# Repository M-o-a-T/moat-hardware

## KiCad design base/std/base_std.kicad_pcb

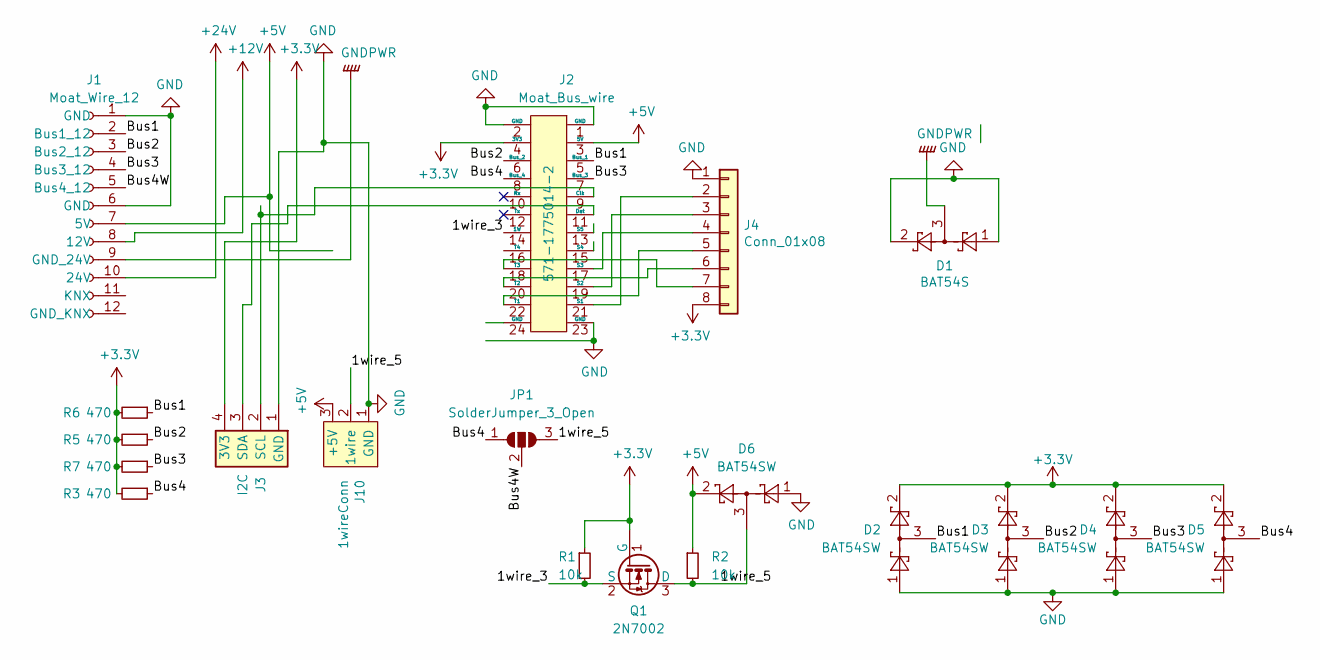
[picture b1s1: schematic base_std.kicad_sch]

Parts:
D1: BAT54S; SOT-23
D2, D3, D4, D5, D6: BAT54SW; SOT-23
J1: Moat_Wire_12; MoaT_12_Pin_V
J2: Moat_Bus_wire; TE_1775014_socket; Digikey A118067CT-ND
J3: I2C; AVX_9276_4Pin_HS
J4: Conn_01x08; PinHeader_1x08_P2.54mm_Vertical
J10: 1wireConn; AVX_9276_3Pin
JP1: SolderJumper_3_Open; SolderJumper-3_P2.0mm_Open_TrianglePad1.0x1.5mm_NumberLabels
Q1: 2N7002; SOT-23
R1, R2: 10k; R_0603_1608Metric
R3, R5, R6, R7: 470; R_0603_1608Metric

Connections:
+3V3: D2.2, D3.2, D4.2, D5.2, J2.4 (3V3), J3.4 (3V3), J4.8, Q1.1 (G), R1.1, R3.2, R5.2, R6.2, R7.2
+5V: D6.2, J1.7 (5V), J2.3 (5V), J10.3 (+5V), R2.1
+12V: J1.8 (12V)
+24V: J1.10 (24V)
/1wire_3: J2.14 (1W), Q1.2 (S), R1.2
/1wire_5: D6.3, J10.2 (1wire), JP1.3 (B), Q1.3 (D), R2.2
/Bus1: D2.3, J1.2 (Bus1_12), J2.5 (Bus_1), R6.1
/Bus2: D3.3, J1.3 (Bus2_12), J2.6 (Bus_2), R5.1
/Bus3: D4.3, J1.4 (Bus3_12), J2.7 (Bus_3), R7.1
/Bus4: D5.3, J2.8 (Bus_4), JP1.1 (A), R3.1
/Bus4W: J1.5 (Bus4_12), JP1.2 (C)
GND: D1.1, D1.2, D2.1, D3.1, D4.1, D5.1, D6.1, J1.1 (GND), J1.6 (GND), J2.1 (GND), J2.2 (GND), J2.23 (GND), J3.1 (GND), J4.1, J10.1 (GND)
GNDPWR: D1.3, J1.9 (GND_24V)
unnamed: J2.9 (Clk), J3.2 (SCL)
unnamed: J2.11 (Dat), J3.3 (SDA)
unnamed: J2.21 (S1), J4.2
unnamed: J2.19 (S2), J4.3
unnamed: J2.17 (S3), J4.4
unnamed: J2.22 (T1), J4.5
unnamed: J2.20 (T2), J4.6
unnamed: J2.18 (T3), J4.7

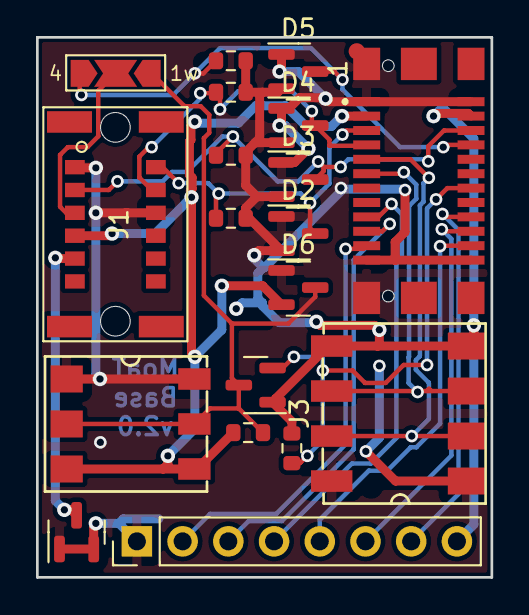
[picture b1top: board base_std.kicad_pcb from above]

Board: 2 copper layers, 25.2 x 30.0 mm, 19 parts (0 on the bottom side), 19 nets.

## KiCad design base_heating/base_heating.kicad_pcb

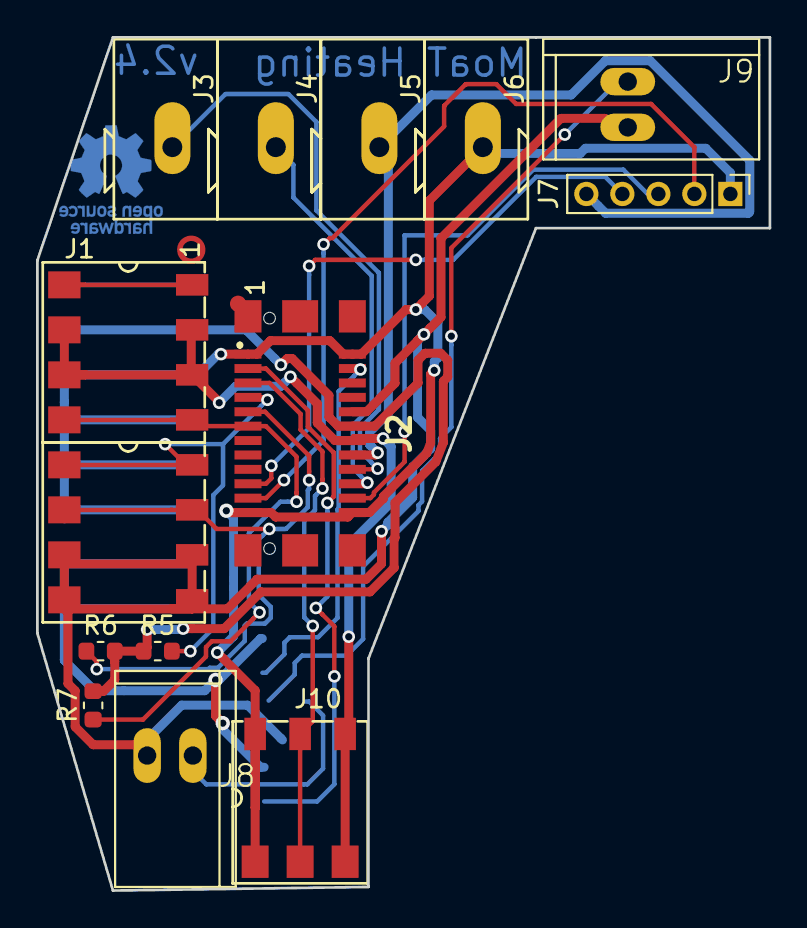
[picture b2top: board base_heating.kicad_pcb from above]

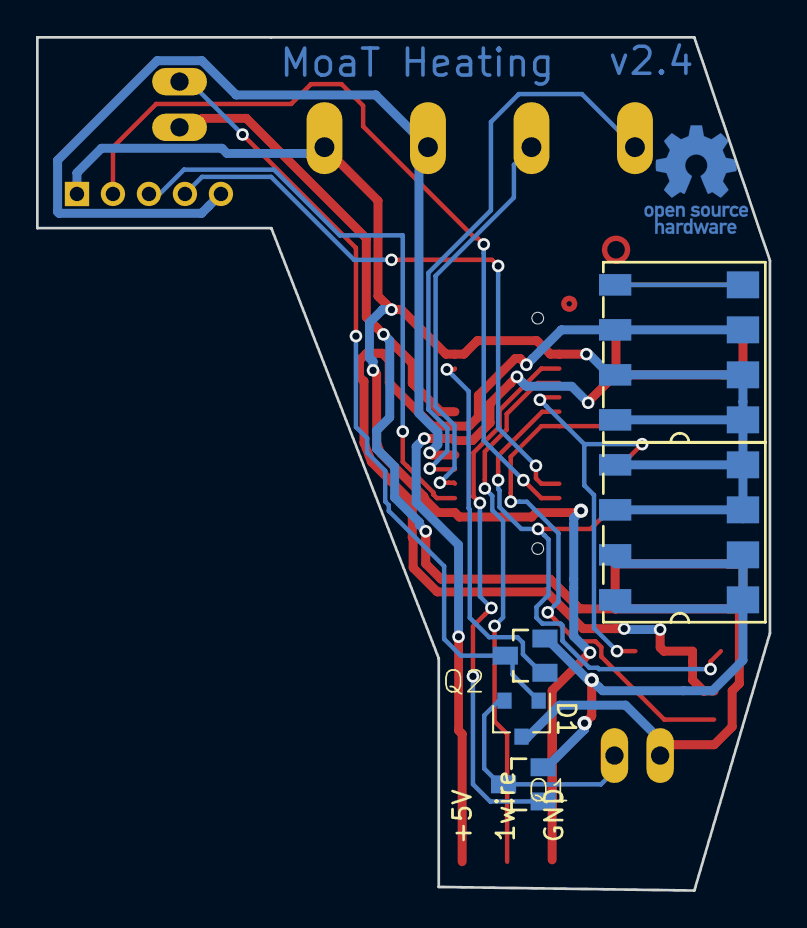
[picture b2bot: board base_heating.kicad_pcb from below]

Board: 2 copper layers, 40.7 x 47.4 mm, 16 parts (3 on the bottom side), 19 nets.

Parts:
D1: BAT54C; SOT-23
J1: Moat_Bus_16; Moat_16_2side
J2: Moat_Bus_wire; TE_1775014_socket
J3: SCLK; Wago_Terminal_243
J4: SDA; Wago_Terminal_243
J5: 3V3; Wago_Terminal_243
J6: GND; Wago_Terminal_243
J7: Conn_01x05; PinHeader_1x05_P2.00mm_Vertical
J8: S1; 1X02_GN
J9: S2; 1X02_GN
J10: 1wireConn; AVX_9276_3Pin
Q1, Q2: 2N7002; SOT23
R5, R6, R7: 470; R_0603_1608Metric

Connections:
+5V: J1.3 (5V), J1.5 (5V), J2.14 (5V), J10.3 (+5V)
+12V: J1.4 (12V), J2.12 (12V), R5.1, R6.2, R7.2
+24V: D1.3, J1.13 (24V), J1.15 (24V), J2.10 (Vcc), J8.2, J9.2
/S1: J2.3 (S1), Q1.1 (G)
/S2: J2.4 (S2), Q2.1 (G)
GNDPWR: J1.14 (GND_24), J1.16 (GND_24), Q1.2 (S), Q2.2 (S)
unnamed: J1.11 (Bus1_12), J2.9 (Bus2_12), R6.1
unnamed: J1.9 (Bus2_12), J2.7 (Bus1_12), R5.2
unnamed: J1.7 (Bus3_12), J2.11 (Bus3_12), R7.1
unnamed: J1.6 (GND), J1.8 (GND), J1.10 (GND), J1.12 (GND), J2.1 (GND), J2.2 (GND), J2.23 (GND), J2.24 (GND), J6.1, J7.1, J10.1 (GND)
unnamed: J2.16 (3V3), J5.1, J7.5
unnamed: J2.18 (CLK), J3.1
unnamed: J2.20 (DAT), J4.1
unnamed: J2.21 (T1), J7.2
unnamed: J2.22 (T2), J7.3
unnamed: J2.19 (T3), J7.4
unnamed: J2.5 (1wire_5), J10.2 (1wire)
unnamed: D1.2, J8.1, Q1.3 (D)
unnamed: D1.1, J9.1, Q2.3 (D)

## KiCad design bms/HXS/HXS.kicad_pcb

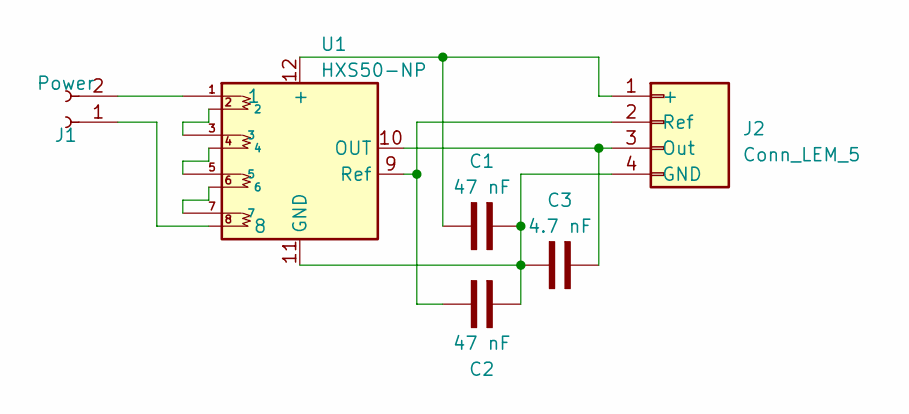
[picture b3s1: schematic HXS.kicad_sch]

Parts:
C1, C2: C_47n_0603; C_0603_1608Metric; Farnell 3013432
C3: C_4n7_0603; C_0603_1608Metric; Farnell 2812325
J1: Power; Conn_P5.0mm_2_Lumberg
J2: Conn_LEM_5; JST_PH_B4B-PH-K_1x04_P2.00mm_Vertical
U1: HXS50-NP; LEM_HXS_50-NP

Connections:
unnamed: J1.2, U1.1
unnamed: C1.1, J2.1 (+), U1.12 (+)
unnamed: C1.2, C2.2, C3.1, J2.4 (GND), U1.11 (GND)
unnamed: C3.2, J2.3 (Out), U1.10 (OUT)
unnamed: C2.1, J2.2 (Ref), U1.9 (Ref)
unnamed: U1.2, U1.3
unnamed: U1.4, U1.5
unnamed: U1.6, U1.7
unnamed: J1.1, U1.8

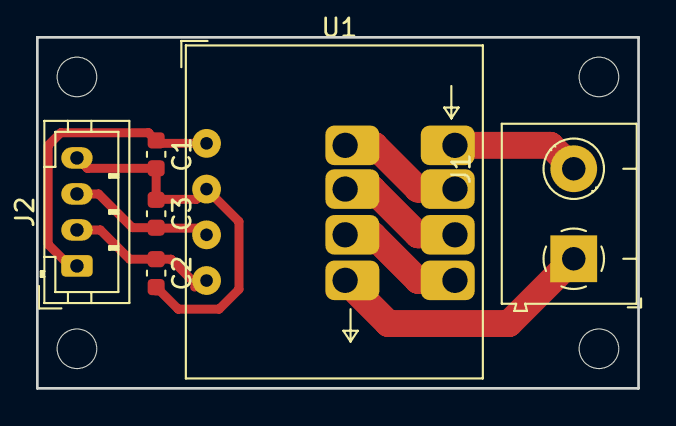
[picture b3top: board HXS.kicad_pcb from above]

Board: 2 copper layers, 33.4 x 19.5 mm, 6 parts (0 on the bottom side), 9 nets.

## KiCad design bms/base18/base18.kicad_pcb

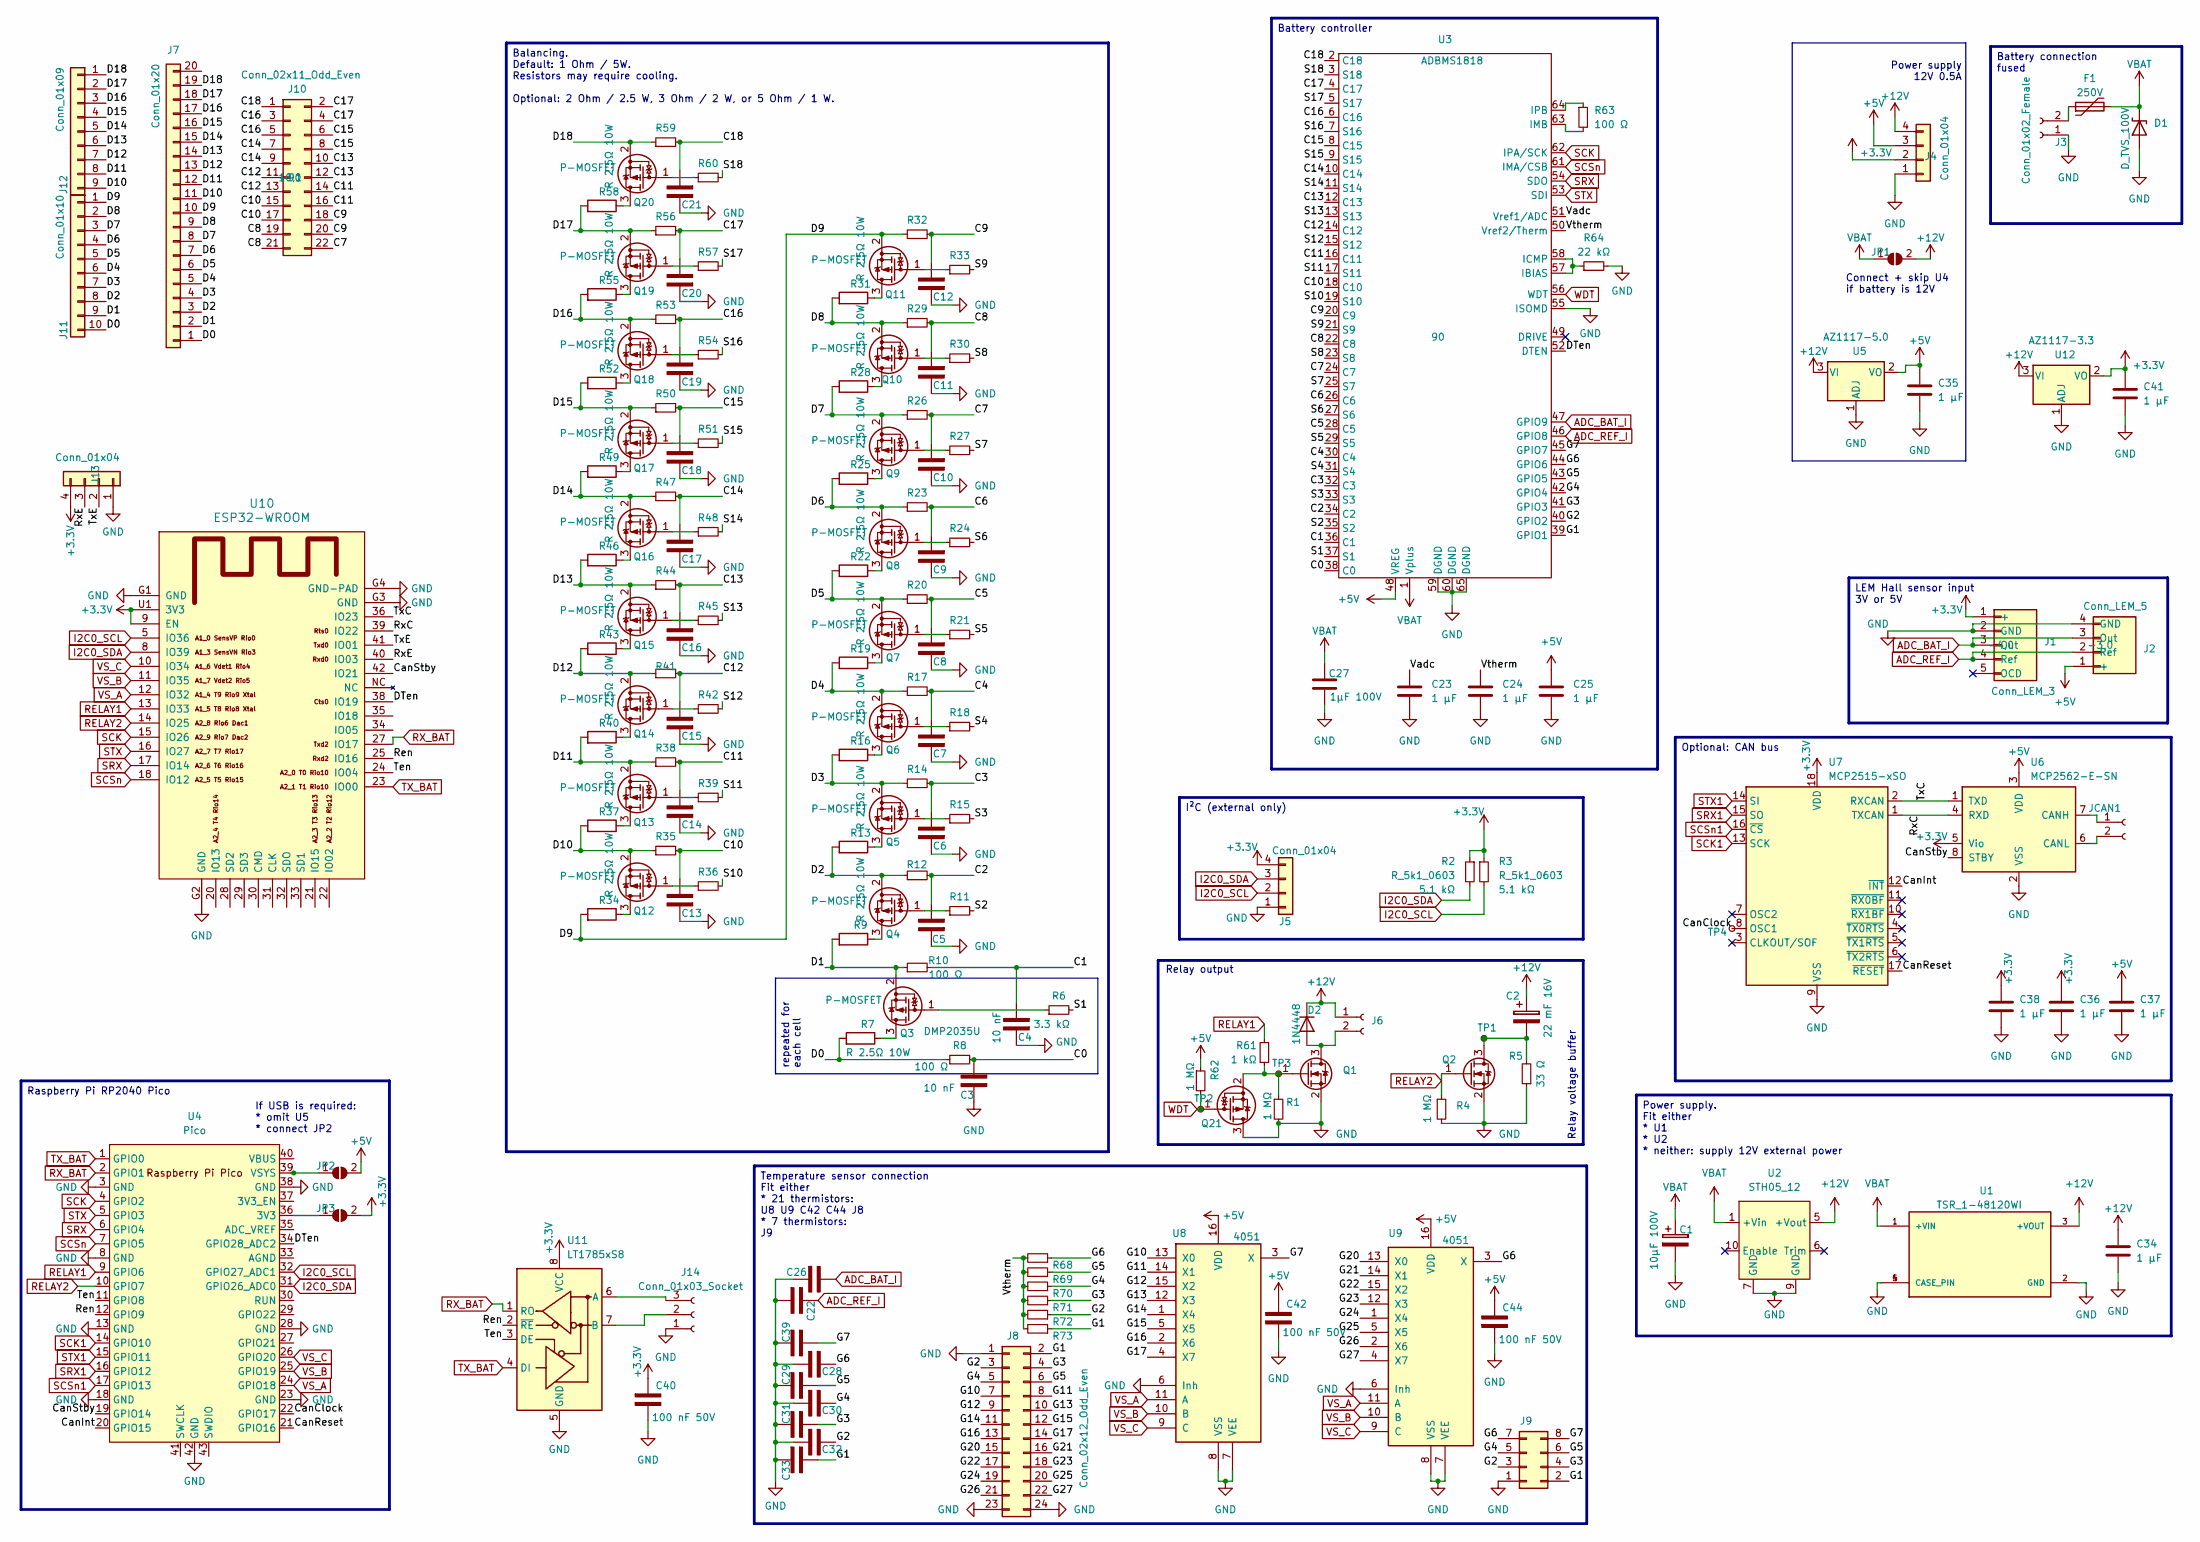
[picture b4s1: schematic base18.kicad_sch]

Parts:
C1: CP_10µ_100V_6m3; CP_Elec_6.3x7.7; Farnell 2068705
C2: CP_22m_16V; CP_Radial_D22.0mm_P10.00mm_SnapIn; LCSC C315548
C3, C4, C5, C6, C7, C8, C9, C10, C11, C12, C13, C14, C15, C16, C17, C18, C19, C20, C21, C22, C26, C28, C29, C30, C31, C32, C33, C39, C40, C42, C44: CP_100n_50V_0603; C_0603_1608Metric; LCSC C14663
C23, C24, C25: CP_1µ_10V_0603; C_0603_1608Metric; Farnell 3013419
C27: CP_1µ_100V_0805; R_0805_2012Metric; Farnell 3243166
C34, C35, C36, C37, C38, C41: C_1µ_25V_0603; C_0603_1608Metric; Farnell 3581460
D1: D_TVS_100V; D_SMB; Farnell 3996927
D2: 1N4448; D_SOD-123; LCSC C124191
F1: FuseHolder; Fuseholder_Cylinder-5x20mm_Stelvio-Kontek_PTF78_Horizontal_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; Farnell 2461158
J1: Conn_LEM_3; JST_PH_B5B-PH-K_1x05_P2.00mm_Vertical; LCSC C157993
J2: Conn_LEM_5; JST_PH_B4B-PH-K_1x04_P2.00mm_Vertical; LCSC C131334
J3: Conn_01x02_Female; Esto02
J4, J5, J13: Conn_01x04; PinHeader_1x04_P2.54mm_Vertical
J6: Conn_01x02_Female; Conn_P5.0mm_2_Lumberg
J7: Conn_01x20; PinHeader_1x20_P2.54mm_Horizontal
J8: Conn_02x12_Odd_Even; PinHeader_2x12_P2.54mm_Vertical
J9: Conn_02x04_Odd_Even; PinHeader_2x04_P2.54mm_Vertical
J10: Conn_02x11_Odd_Even; PinHeader_2x11_P2.00mm_Vertical; LCSC C2905997
J11: Conn_01x10; PinSocket_1x10_P2.00mm_Horizontal; LCSC C158038
J12: Conn_01x09; PinSocket_1x09_P2.00mm_Horizontal; LCSC C157968
J14: Conn_01x03_Socket; PinHeader_1x03_P2.54mm_Vertical
JCAN1: Conn_01x02_Female; Esto02
JP1, JP2, JP3: Bat12V; SolderJumper-2_P1.3mm_Open_RoundedPad1.0x1.5mm
Q1, Q2: DMN2058U; SOT-23; Farnell 2709530
Q3, Q4, Q5, Q6, Q7, Q8, Q9, Q10, Q11, Q12, Q13, Q14, Q15, Q16, Q17, Q18, Q19, Q20, Q21: DMP2035U; SOT-23; Farnell 2061419
R1, R4, R62: R_1M_0603; R_0603_1608Metric; LCSC C22935
R2, R3: R_5k1_0603; R_0603_1608Metric; LCSC C23186
R5: R_33_0603; R_0603_1608Metric; LCSC C25232
R6, R11, R15, R18, R21, R24, R27, R30, R33, R36, R39, R42, R45, R48, R51, R54, R57, R60: R_3k3_0603; R_0603_1608Metric; LCSC C22978
R7, R9, R13, R16, R19, R22, R25, R28, R31, R34, R37, R40, R43, R46, R49, R52, R55, R58: R_2.5_10W; R_Radial_Power_L12.5mm_W9.0mm_P5.00mm; LCSC C216394
R8, R10, R12, R14, R17, R20, R23, R26, R29, R32, R35, R38, R41, R44, R47, R50, R53, R56, R59, R63: R_100_0603; R_0603_1608Metric; LCSC C22775
R61: R_1k_0603; R_0603_1608Metric; LCSC C21190
R64: R_22k_0603; R_0603_1608Metric; LCSC C31850
R68, R69, R70, R71, R72, R73: R_10k_0603; R_0603_1608Metric; LCSC C25804
TP1, TP2, TP3, TP4: TestPoint_Small; TestPoint_Pad_D1.0mm
U1: TSR_1-48120WI; TSR_1-48xxWI; PARTREV April 7, 2021; Farnell 3255316
U2: STH05_12; STH05; Farnell 3212472
U3: ADBMS1818; LQFP-64-1EP_10x10mm_P0.5mm_EP5x5mm_ThermalVias; Farnell 4027982
U4: Pico; RPi_Pico_SMD
U5: AZ1117-5.0; SOT-223; LCSC C526405
U6: MCP2562-E-SN; SOIC-8_3.9x4.9mm_P1.27mm; JLCRotOffset -90
U7: MCP2515-xSO; SOIC-18W_7.5x11.6mm_P1.27mm; Farnell 1605565
U8, U9: 4051; SOIC-16_3.9x9.9mm_P1.27mm; Farnell 1201327
U10: ESP32-WROOM; Digikey 1904-1024-1-ND
U11: LT1785xS8; SOIC-8_3.9x4.9mm_P1.27mm; LCSC C468242
U12: AZ1117-3.3; SOT-223; LCSC C108492

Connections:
+3V3: C36.1, C38.1, C40.1, C41.1, J1.1 (+), J4.2, J5.4, J13.4, JP3.2 (B), R2.1, R3.1, U6.5 (Vio), U7.18 (VDD), U10.9 (EN), U10.U1 (3V3), U11.8 (VCC), U12.2 (VO)
+5V: C25.1, C35.1, C37.1, C42.1, C44.1, J2.1 (+), J4.3, JP2.2 (B), R62.1, U3.48 (VREG), U5.2 (VO), U6.3 (VDD), U8.16 (VDD), U9.16 (VDD)
+12V: C2.1, C34.1, D2.1 (K), J4.4, J6.1, JP1.2 (B), U1.3 (+VOUT), U2.5 (+Vout), U5.3 (VI), U12.3 (VI)
/C0: C3.1, R8.2, U3.38 (C0)
/C1: C4.1, R10.2, U3.36 (C1)
/C2: C5.1, R12.2, U3.34 (C2)
/C3: C6.1, R14.2, U3.32 (C3)
/C4: C7.1, R17.2, U3.30 (C4)
/C5: C8.1, R20.2, U3.28 (C5)
/C6: C9.1, R23.2, U3.26 (C6)
/C7: C10.1, J10.22, R26.2, U3.24 (C7)
/C8: C11.1, J10.19, J10.21, R29.2, U3.22 (C8)
/C9: C12.1, J10.18, J10.20, R32.2, U3.20 (C9)
/C10: C13.1, J10.15, J10.17, R35.2, U3.18 (C10)
/C11: C14.1, J10.14, J10.16, R38.2, U3.16 (C11)
/C12: C15.1, J10.11, J10.13, R41.2, U3.14 (C12)
/C13: C16.1, J10.10, J10.12, R44.2, U3.12 (C13)
/C14: C17.1, J10.7, J10.9, R47.2, U3.10 (C14)
/C15: C18.1, J10.6, J10.8, R50.2, U3.8 (C15)
/C16: C19.1, J10.3, J10.5, R53.2, U3.6 (C16)
/C17: C20.1, J10.2, J10.4, R56.2, U3.4 (C17)
/C18: C21.1, J10.1, R59.2, U3.2 (C18)
/CanClock: TP4.1, U4.22 (GPIO17), U7.8 (OSC1)
/CanInt: U4.20 (GPIO15), U7.12 (~INT)
/CanReset: U4.21 (GPIO16), U7.17 (~RESET)
/CanStby: U4.19 (GPIO14), U6.8 (STBY), U10.42 (IO21)
/D0: J7.1, J11.10, R7.2, R8.1
/D1: J7.2, J11.9, Q3.2 (S), R9.2, R10.1
/D2: J7.3, J11.8, Q4.2 (S), R12.1, R13.2
/D3: J7.4, J11.7, Q5.2 (S), R14.1, R16.2
/D4: J7.5, J11.6, Q6.2 (S), R17.1, R19.2
/D5: J7.6, J11.5, Q7.2 (S), R20.1, R22.2
/D6: J7.7, J11.4, Q8.2 (S), R23.1, R25.2
/D7: J7.8, J11.3, Q9.2 (S), R26.1, R28.2
/D8: J7.9, J11.2, Q10.2 (S), R29.1, R31.2
/D9: J7.10, J11.1, Q11.2 (S), R32.1, R34.2
/D10: J7.11, J12.9, Q12.2 (S), R35.1, R37.2
/D11: J7.12, J12.8, Q13.2 (S), R38.1, R40.2
/D12: J7.13, J12.7, Q14.2 (S), R41.1, R43.2
/D13: J7.14, J12.6, Q15.2 (S), R44.1, R46.2
/D14: J7.15, J12.5, Q16.2 (S), R47.1, R49.2
/D15: J7.16, J12.4, Q17.2 (S), R50.1, R52.2
/D16: J7.17, J12.3, Q18.2 (S), R53.1, R55.2
/D17: J7.18, J12.2, Q19.2 (S), R56.1, R58.2
/D18: J7.19, J12.1, Q20.2 (S), R59.1
/DTen: U3.52 (DTEN), U4.34 (GPIO28_ADC2), U10.38 (IO19)
/G1: C33.2, J8.2, J9.2, R73.1, U3.39 (GPIO1)
/G2: C32.2, J8.3, J9.3, R72.1, U3.40 (GPIO2)
/G3: C31.2, J8.4, J9.4, R71.1, U3.41 (GPIO3)
/G4: C30.2, J8.5, J9.5, R70.1, U3.42 (GPIO4)
/G5: C29.2, J8.6, J9.6, R69.1, U3.43 (GPIO5)
/G6: C28.2, J9.7, R68.1, U3.44 (GPIO6), U9.3 (X)
/G7: C39.2, J9.8, U3.45 (GPIO7), U8.3 (X)
/G10: J8.7, U8.13 (X0)
/G11: J8.8, U8.14 (X1)
/G12: J8.9, U8.15 (X2)
/G13: J8.10, U8.12 (X3)
/G14: J8.11, U8.1 (X4)
/G15: J8.12, U8.5 (X5)
/G16: J8.13, U8.2 (X6)
/G17: J8.14, U8.4 (X7)
/G20: J8.15, U9.13 (X0)
/G21: J8.16, U9.14 (X1)
/G22: J8.17, U9.15 (X2)
/G23: J8.18, U9.12 (X3)
/G24: J8.19, U9.1 (X4)
/G25: J8.20, U9.5 (X5)
/G26: J8.21, U9.2 (X6)
/G27: J8.22, U9.4 (X7)
/Ren: U4.12 (GPIO9), U10.25 (IO16), U11.2 (~RE)
/RxC: U6.4 (RXD), U7.1 (TXCAN), U10.39 (IO22)
/RxE: J13.3, U10.40 (IO03)
/S1: R6.2, U3.37 (S1)
/S2: R11.2, U3.35 (S2)
/S3: R15.2, U3.33 (S3)
/S4: R18.2, U3.31 (S4)
/S5: R21.2, U3.29 (S5)
/S6: R24.2, U3.27 (S6)
/S7: R27.2, U3.25 (S7)
/S8: R30.2, U3.23 (S8)
/S9: R33.2, U3.21 (S9)
/S10: R36.2, U3.19 (S10)
/S11: R39.2, U3.17 (S11)
/S12: R42.2, U3.15 (S12)
/S13: R45.2, U3.13 (S13)
/S14: R48.2, U3.11 (S14)
/S15: R51.2, U3.9 (S15)
/S16: R54.2, U3.7 (S16)
/S17: R57.2, U3.5 (S17)
/S18: R60.2, U3.3 (S18)
/Ten: U4.11 (GPIO8), U10.24 (IO04), U11.3 (DE)
/TxC: U6.1 (TXD), U7.2 (RXCAN), U10.36 (IO23)
/TxE: J13.2, U10.41 (IO01)
/Vadc: C23.1, U3.51 (Vref1/ADC)
/Vtherm: C24.1, R68.2, R69.2, R70.2, R71.2, R72.2, R73.2, U3.50 (Vref2/Therm)
ADC_BAT_I: C26.2, J1.3 (Out), J2.3 (Out), U3.47 (GPIO9)
ADC_REF_I: C22.2, J1.4 (Ref), J2.2 (Ref), U3.46 (GPIO8)
GND: C1.2, C3.2, C4.2, C5.2, C6.2, C7.2, C8.2, C9.2, C10.2, C11.2, C12.2, C13.2, C14.2, C15.2, C16.2, C17.2, C18.2, C19.2, C20.2, C21.2, C22.1, C23.2, C24.2, C25.2, C26.1, C27.2, C28.1, C29.1, C30.1, C31.1, C32.1, C33.1, C34.2, C35.2, C36.2, C37.2, C38.2, C39.1, C40.2, C41.2, C42.2, C44.2, D1.2 (A), J1.2 (GND), J2.4 (GND), J3.1, J4.1, J5.1, J8.1, J8.23, J8.24, J9.1, J13.1, J14.1, Q1.2 (S), Q2.2 (S), Q21.3 (D), R1.2, R4.2, R5.1, R64.2, U1.2 (GND), U1.4 (CASE_PIN), U1.5 (CASE_PIN), U2.7 (GND), U2.9 (GND), U3.55 (ISOMD), U3.59 (DGND), U3.60 (DGND), U3.65 (DGND), U4.3 (GND), U4.8 (GND), U4.13 (GND), U4.18 (GND), U4.23 (GND), U4.28 (GND), U4.38 (GND), U4.42 (GND), U5.1 (ADJ), U6.2 (VSS), U7.9 (VSS), U8.6 (Inh), U8.7 (VEE), U8.8 (VSS), U9.6 (Inh), U9.7 (VEE), U9.8 (VSS), U10.G1 (GND), U10.G2 (GND), U10.G3 (GND), U10.G4 (GND-PAD), U11.5 (GND), U12.1 (ADJ)
I2C0_SCL: J5.2, R3.2, U4.32 (GPIO27_ADC1), U10.5 (IO36)
I2C0_SDA: J5.3, R2.2, U4.31 (GPIO26_ADC0), U10.8 (IO39)
unnamed: D2.2 (A), J6.2, Q1.3 (D)
unnamed: F1.1, J3.2
unnamed: J14.2, U11.7 (B)
unnamed: J14.3, U11.6 (A)
unnamed: JCAN1.1, U6.7 (CANH)
unnamed: JCAN1.2, U6.6 (CANL)
unnamed: JP2.1 (A), U4.39 (VSYS)
unnamed: JP3.1 (A), U4.36 (3V3)
unnamed: Q1.1 (G), Q21.2 (S), R1.1, R61.2, TP3.1
unnamed: C2.2, Q2.3 (D), R5.2, TP1.1
unnamed: Q3.3 (D), R7.1
unnamed: Q3.1 (G), R6.1
unnamed: Q4.3 (D), R9.1
unnamed: Q4.1 (G), R11.1
unnamed: Q5.3 (D), R13.1
unnamed: Q5.1 (G), R15.1
unnamed: Q6.3 (D), R16.1
unnamed: Q6.1 (G), R18.1
unnamed: Q7.3 (D), R19.1
unnamed: Q7.1 (G), R21.1
unnamed: Q8.3 (D), R22.1
unnamed: Q8.1 (G), R24.1
unnamed: Q9.3 (D), R25.1
unnamed: Q9.1 (G), R27.1
unnamed: Q10.3 (D), R28.1
unnamed: Q10.1 (G), R30.1
unnamed: Q11.3 (D), R31.1
unnamed: Q11.1 (G), R33.1
unnamed: Q12.3 (D), R34.1
unnamed: Q12.1 (G), R36.1
unnamed: Q13.3 (D), R37.1
unnamed: Q13.1 (G), R39.1
unnamed: Q14.3 (D), R40.1
unnamed: Q14.1 (G), R42.1
unnamed: Q15.3 (D), R43.1
unnamed: Q15.1 (G), R45.1
unnamed: Q16.3 (D), R46.1
unnamed: Q16.1 (G), R48.1
unnamed: Q17.3 (D), R49.1
unnamed: Q17.1 (G), R51.1
unnamed: Q18.3 (D), R52.1
unnamed: Q18.1 (G), R54.1
unnamed: Q19.3 (D), R55.1
unnamed: Q19.1 (G), R57.1
unnamed: Q20.3 (D), R58.1
unnamed: Q20.1 (G), R60.1
unnamed: R64.1, U3.57 (IBIAS), U3.58 (ICMP)
unnamed: R63.2, U3.63 (IMB)
unnamed: R63.1, U3.64 (IPB)
RELAY1: R61.1, U4.9 (GPIO6), U10.13 (IO33)
RELAY2: Q2.1 (G), R4.1, U4.10 (GPIO7), U10.14 (IO25)
RX_BAT: U4.2 (GPIO1), U10.27 (IO17), U11.1 (RO)
SCK: U3.62 (IPA/SCK), U4.4 (GPIO2), U10.15 (IO26)
SCK1: U4.14 (GPIO10), U7.13 (SCK)
SCSn: U3.61 (IMA/CSB), U4.7 (GPIO5), U10.18 (IO12)
SCSn1: U4.17 (GPIO13), U7.16 (~CS)
SRX: U3.54 (SDO), U4.6 (GPIO4), U10.17 (IO14)
SRX1: U4.16 (GPIO12), U7.15 (SO)
STX: U3.53 (SDI), U4.5 (GPIO3), U10.16 (IO27)
STX1: U4.15 (GPIO11), U7.14 (SI)
TX_BAT: U4.1 (GPIO0), U10.23 (IO00), U11.4 (DI)
VBAT: C1.1, C27.1, D1.1 (K), F1.2, JP1.1 (A), U1.1 (+VIN), U2.1 (+Vin), U3.1 (Vplus)
VS_A: U4.24 (GPIO18), U8.11 (A), U9.11 (A), U10.12 (IO32)
VS_B: U4.25 (GPIO19), U8.10 (B), U9.10 (B), U10.11 (IO35)
VS_C: U4.26 (GPIO20), U8.9 (C), U9.9 (C), U10.10 (IO34)
WDT: Q21.1 (G), R62.2, TP2.1, U3.56 (WDT)

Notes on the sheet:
Battery controller
Battery connection fused
Optional: CAN bus
Power supply. Fit either * U1 * U2 * neither: supply 12V external power
Balancing. Default: 1 Ohm / 5W. Resistors may require cooling. Optional: 2 Ohm / 2.5 W, 3 Ohm / 2 W, or 5 Ohm / 1 W.
Raspberry Pi RP2040 Pico
Temperature sensor connection Fit either * 21 thermistors: U8 U9 C42 C44 J8 * 7 thermistors: J9
I²C (external only)
repeated for each cell
LEM Hall sensor input 3V or 5V
If USB is required: * omit U5 * connect JP2
Power supply 12V 0.5A
Relay output
Relay voltage buffer
Connect + skip U4 if battery is 12V

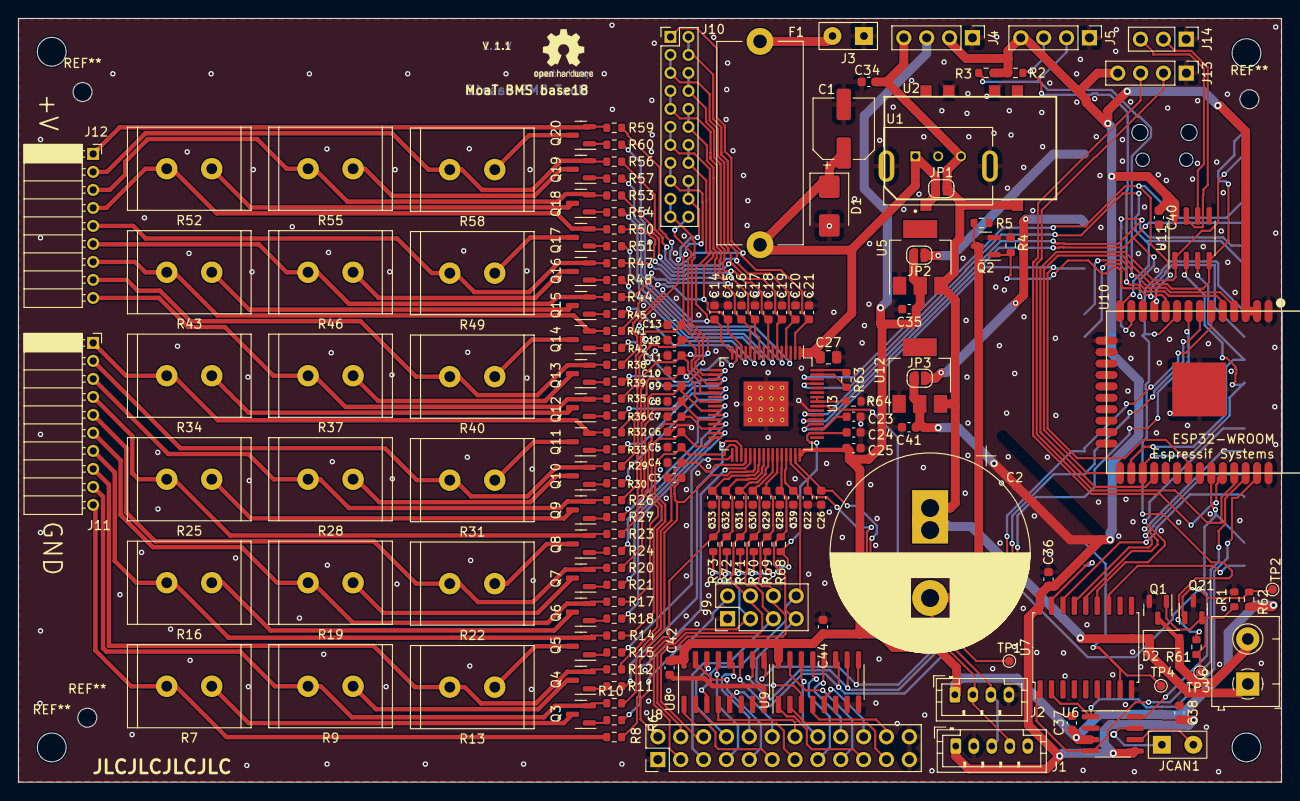
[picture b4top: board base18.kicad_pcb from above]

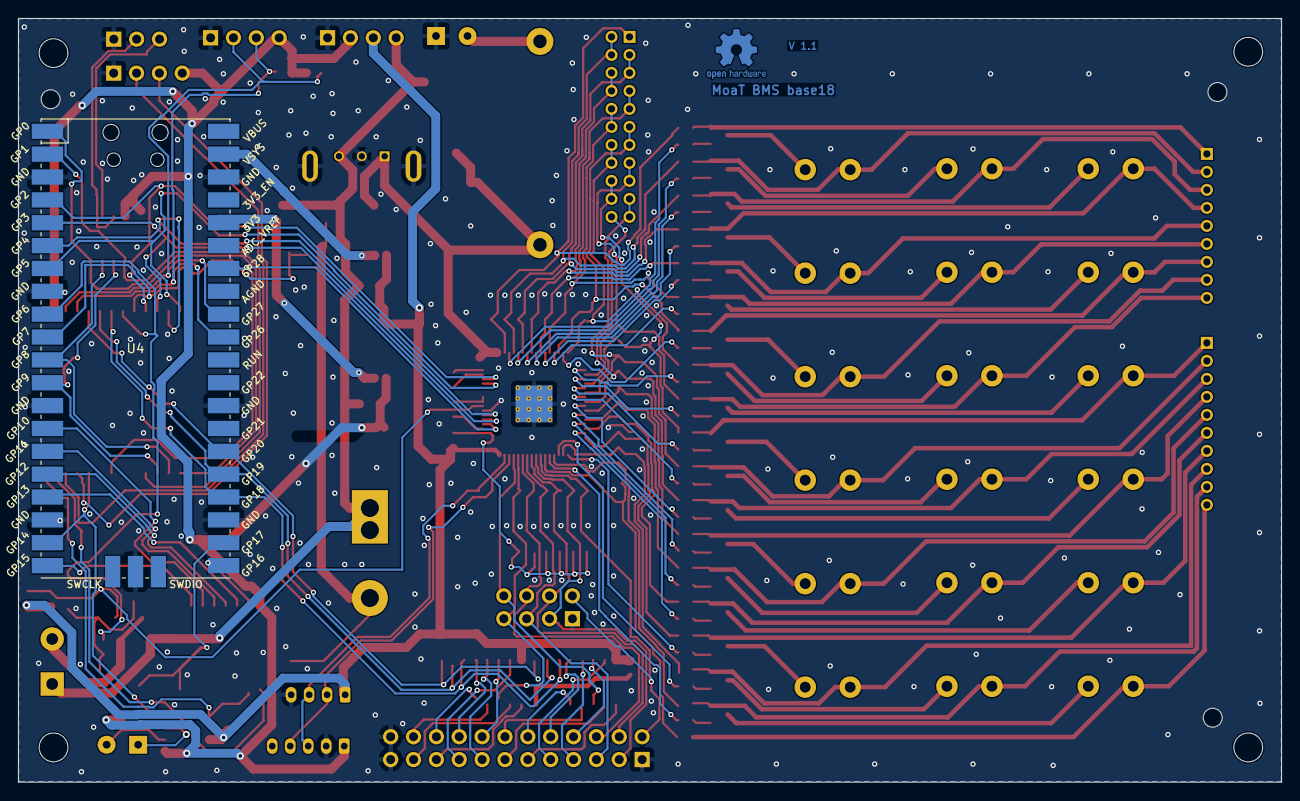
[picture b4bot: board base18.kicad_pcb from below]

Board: 2 copper layers, 140.4 x 84.8 mm, 172 parts (2 on the bottom side), 166 nets.

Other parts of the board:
OSHW Cu: OSHW-Logo2_7.3x6mm_Copper
OSHW Silk: OSHW-Logo2_7.3x6mm_SilkScreen

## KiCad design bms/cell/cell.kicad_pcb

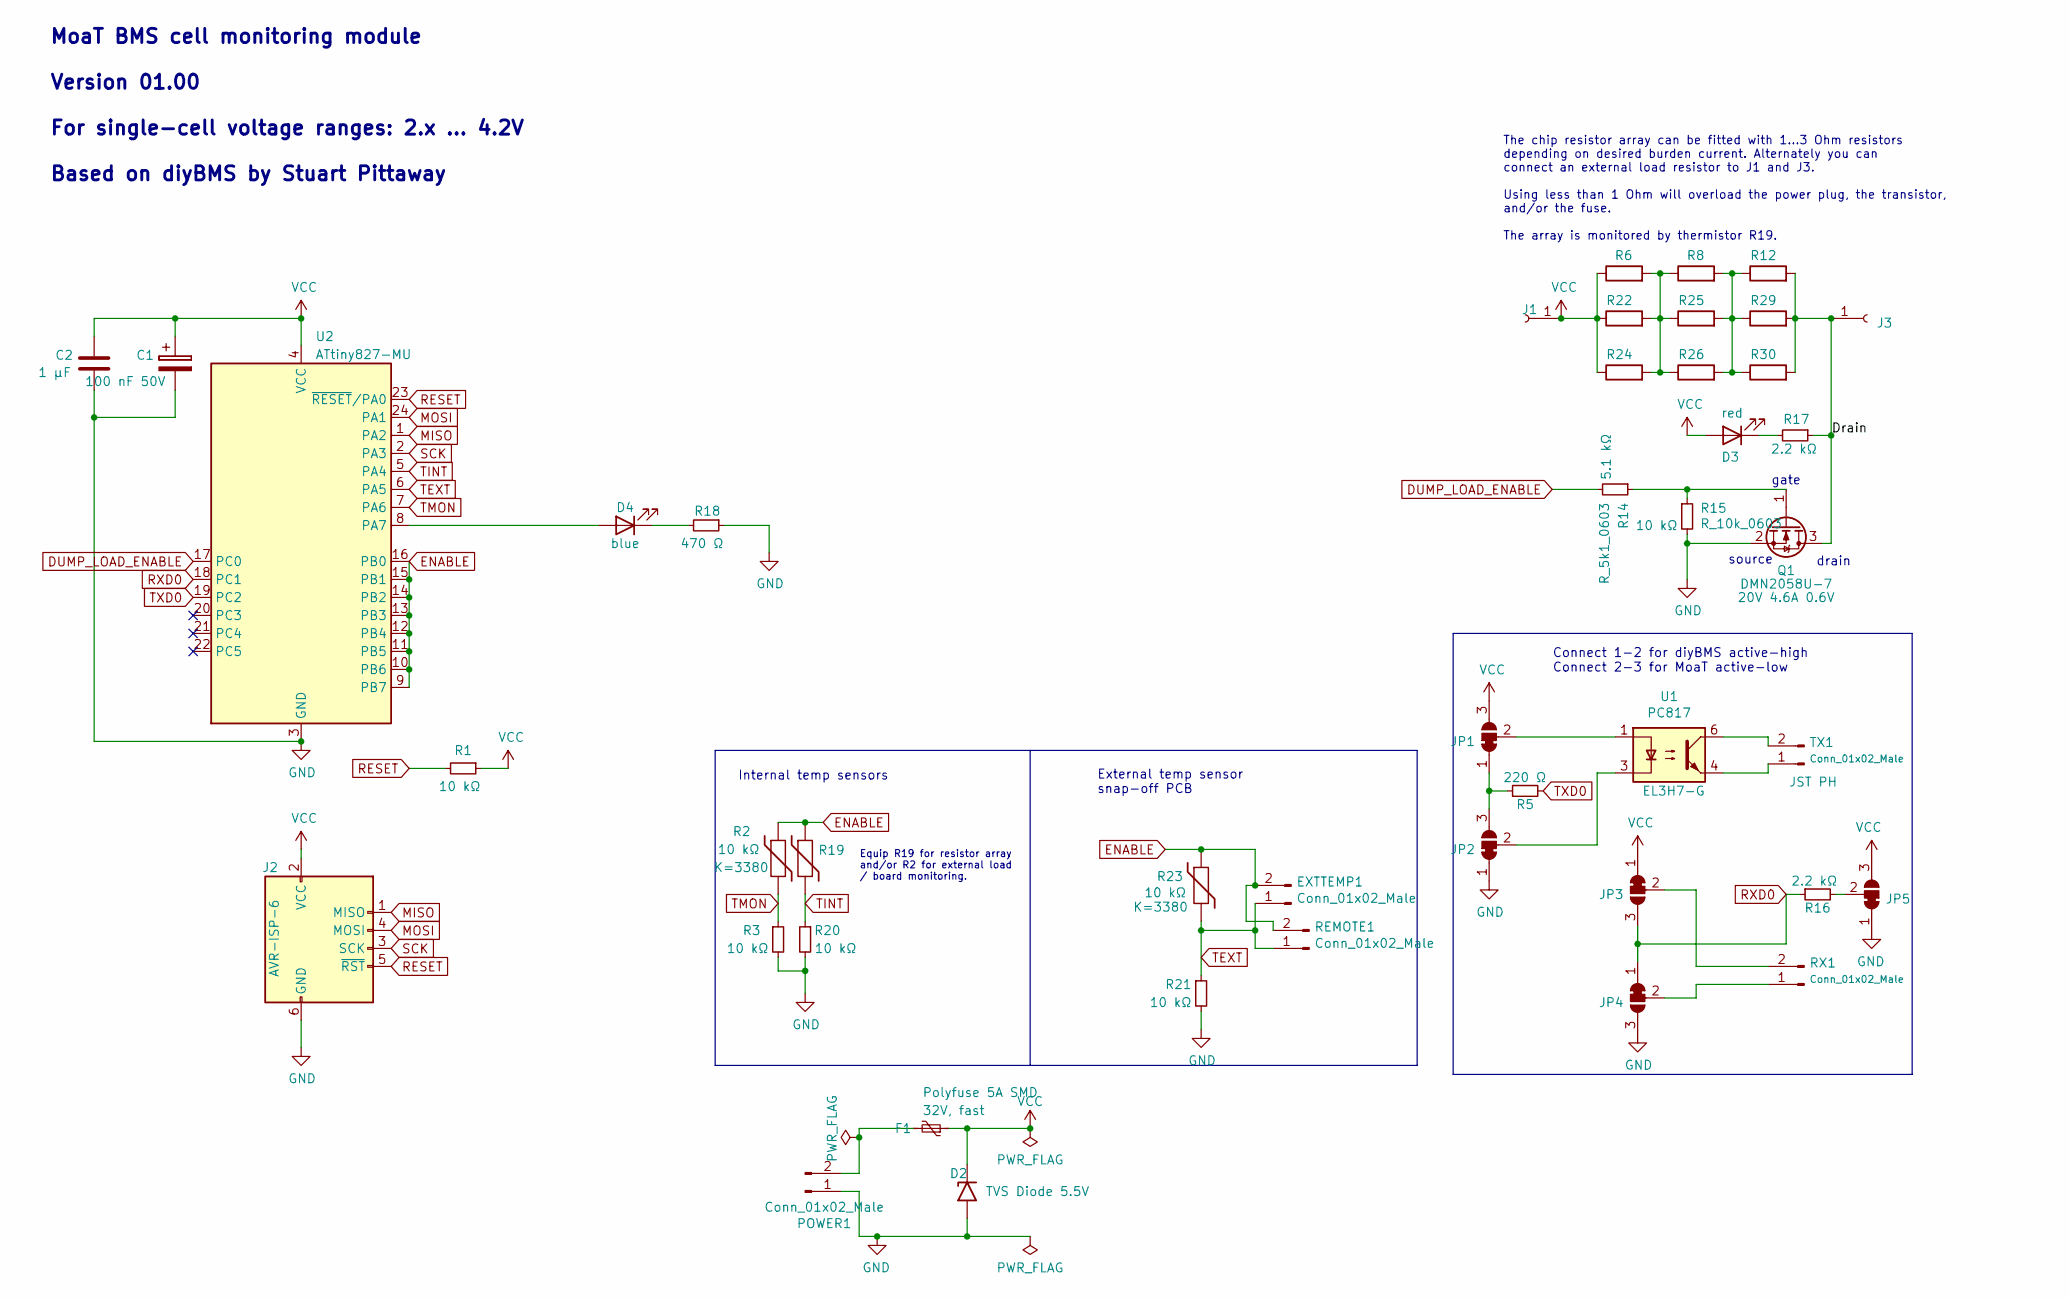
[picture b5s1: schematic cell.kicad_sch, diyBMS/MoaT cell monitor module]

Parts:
C1: CP_100n_50V_0603; C_0603_1608Metric; PartNumber CC0805KRX7R9BB104; LCSCStockCode C49678
C2: CP_1µ_10V_0603; C_0603_1608Metric; Farnell 3013419
D2: SMBJ6.0CD-M3/H; D_SMB; Farnell 2728715
D3: LS R976; LED_0805_2012Metric; Farnell 2846594
D4: LED KPTD-2012LVQBC-D; LED_0805_2012Metric; Farnell 2846594
EXTTEMP1: Conn_01x02_Male; JST_PH_S2B-PH-K_1x02_P2.00mm_Horizontal; PartNumber S2B-PH-K(LF)(SN); LCSCStockCode C265016
F1: MP005460; Fuse_0603_1608Metric; Farnell 3564719
J1, J3: Conn_01x01_Female; TestPoint_THTPad_D2.5mm_Drill1.2mm
J2: AVR-ISP-6; 2X3_PAD
JP1, JP2, JP3, JP4, JP5: SolderJumper_3_Bridged12; SolderJumper-3_P1.3mm_Open_Pad1.0x1.5mm
POWER1: Conn_01x02_Male; JST_XH_S2B-XH-A-1_1x02_P2.50mm_Horizontal
Q1: Q_NMOS_20V_4A_lowVth; SOT-23; Farnell 2709530
R1, R3, R20, R21: R_10k_0603; R_0603_1608Metric
R2, R19, R23: Rth_10k_SMD; R_0603_1608Metric; Farnell 2614207
R5: R_220_0603; R_0603_1608Metric; PartNumber 0805W8F2200T5E; LCSC C17557
R6, R8, R12, R22, R24, R25, R26, R29, R30: R_1_2W; R_2010_5025Metric
R14: R_5k1_0603; R_0603_1608Metric
R15: R_10k_0603; R_0603_1608Metric; PartNumber 0805W8F1002T5E
R16: R_2k2_0603; R_0603_1608Metric
R17: R_2k2_0603; R_0603_1608Metric; PartNumber 0805W8F2201T5E
R18: R_470_0603; R_0603_1608Metric
REMOTE1: Conn_01x02_Male; PinHeader_1x02_P2.54mm_Vertical
RX1: Conn_01x02_Male; JST_PH_S2B-PH-K_1x02_P2.00mm_Horizontal; PartNumber S2B-PH-K(LF)(SN); LCSCStockCode C265016
TX1: Conn_01x02_Male; JST_PH_S2B-PH-K_1x02_P2.00mm_Horizontal; PartNumber S2B-PH-K(LF)(SN); LCSC C265016
U1: PC817; MFSOP6-4_4.4x3.6mm_P1.27mm; Farnell 3397435
U2: ATtiny827-MU; QFN-24-1EP_4x4mm_P0.5mm_EP2.6x2.6mm; Farnell 3630578

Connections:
/Drain: J3.1, Q1.3 (D), R12.2, R17.1, R29.2, R30.2
DUMP_LOAD_ENABLE: R14.2, U2.17 (PC0)
ENABLE: EXTTEMP1.2, R2.1, R19.1, R23.1, REMOTE1.2, U2.9 (PB7), U2.10 (PB6), U2.11 (PB5), U2.12 (PB4), U2.13 (PB3), U2.14 (PB2), U2.15 (PB1), U2.16 (PB0)
GND: C1.2, C2.2, D2.2 (A2), J2.6 (GND), JP2.1 (A), JP4.3 (B), JP5.1 (A), POWER1.1, Q1.2 (S), R3.2, R15.2, R18.1, R20.2, R21.2, U2.3 (GND), U2.25 (GND)
MISO: J2.1 (MISO), U2.1 (PA2)
MOSI: J2.4 (MOSI), U2.24 (PA1)
unnamed: D3.1 (K), R17.2
unnamed: D4.2 (A), U2.8 (PA7)
unnamed: D4.1 (K), R18.2
unnamed: F1.2, POWER1.2
unnamed: Q1.1 (G), R14.1, R15.1
unnamed: JP1.1 (A), JP2.3 (B), R5.1
unnamed: R8.2, R12.1, R25.2, R26.2, R29.1, R30.1
unnamed: JP5.2 (C), R16.2
unnamed: R6.2, R8.1, R22.2, R24.2, R25.1, R26.1
unnamed: JP4.2 (C), RX1.1
unnamed: JP3.2 (C), RX1.2
unnamed: TX1.1, U1.4
unnamed: TX1.2, U1.6
unnamed: JP1.2 (C), U1.1
unnamed: JP2.2 (C), U1.3
RESET: J2.5 (~RST), R1.2, U2.23 (~RESET/PA0)
RXD0: JP3.3 (B), JP4.1 (A), R16.1, U2.18 (PC1)
SCK: J2.3 (SCK), U2.2 (PA3)
TEXT: EXTTEMP1.1, R21.1, R23.2, REMOTE1.1, U2.6 (PA5)
TINT: R19.2, R20.1, U2.5 (PA4)
TMON: R2.2, R3.1, U2.7 (PA6)
TXD0: R5.2, U2.19 (PC2)
VCC: C1.1, C2.1, D2.1 (A1), D3.2 (A), F1.1, J1.1, J2.2 (VCC), JP1.3 (B), JP3.1 (A), JP5.3 (B), R1.1, R6.1, R22.1, R24.1, U2.4 (VCC)

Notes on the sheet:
External temp sensor snap-off PCB
The chip resistor array can be fitted with 1…3 Ohm resistors depending on desired burden current. Alternately you can connect an external load resistor to J1 and J3. Using less than 1 Ohm will overload the power plug, the transistor, and/or the fuse. The array is monitored by thermistor R19.
source
Connect 1-2 for diyBMS active-high Connect 2-3 for MoaT active-low
gate
drain
MoaT BMS cell monitoring module Version 01.00 For single-cell voltage ranges: 2.x … 4.2V Based on diyBMS by Stuart Pittaway
Equip R19 for resistor array and/or R2 for external load / board monitoring.
Internal temp sensors

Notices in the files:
bms/cell/cell.kicad_pcb:
©2019-2021
MoaT mod ©2022
